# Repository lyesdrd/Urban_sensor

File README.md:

# Urban_sensor
Project of embeded crosswalk recognition

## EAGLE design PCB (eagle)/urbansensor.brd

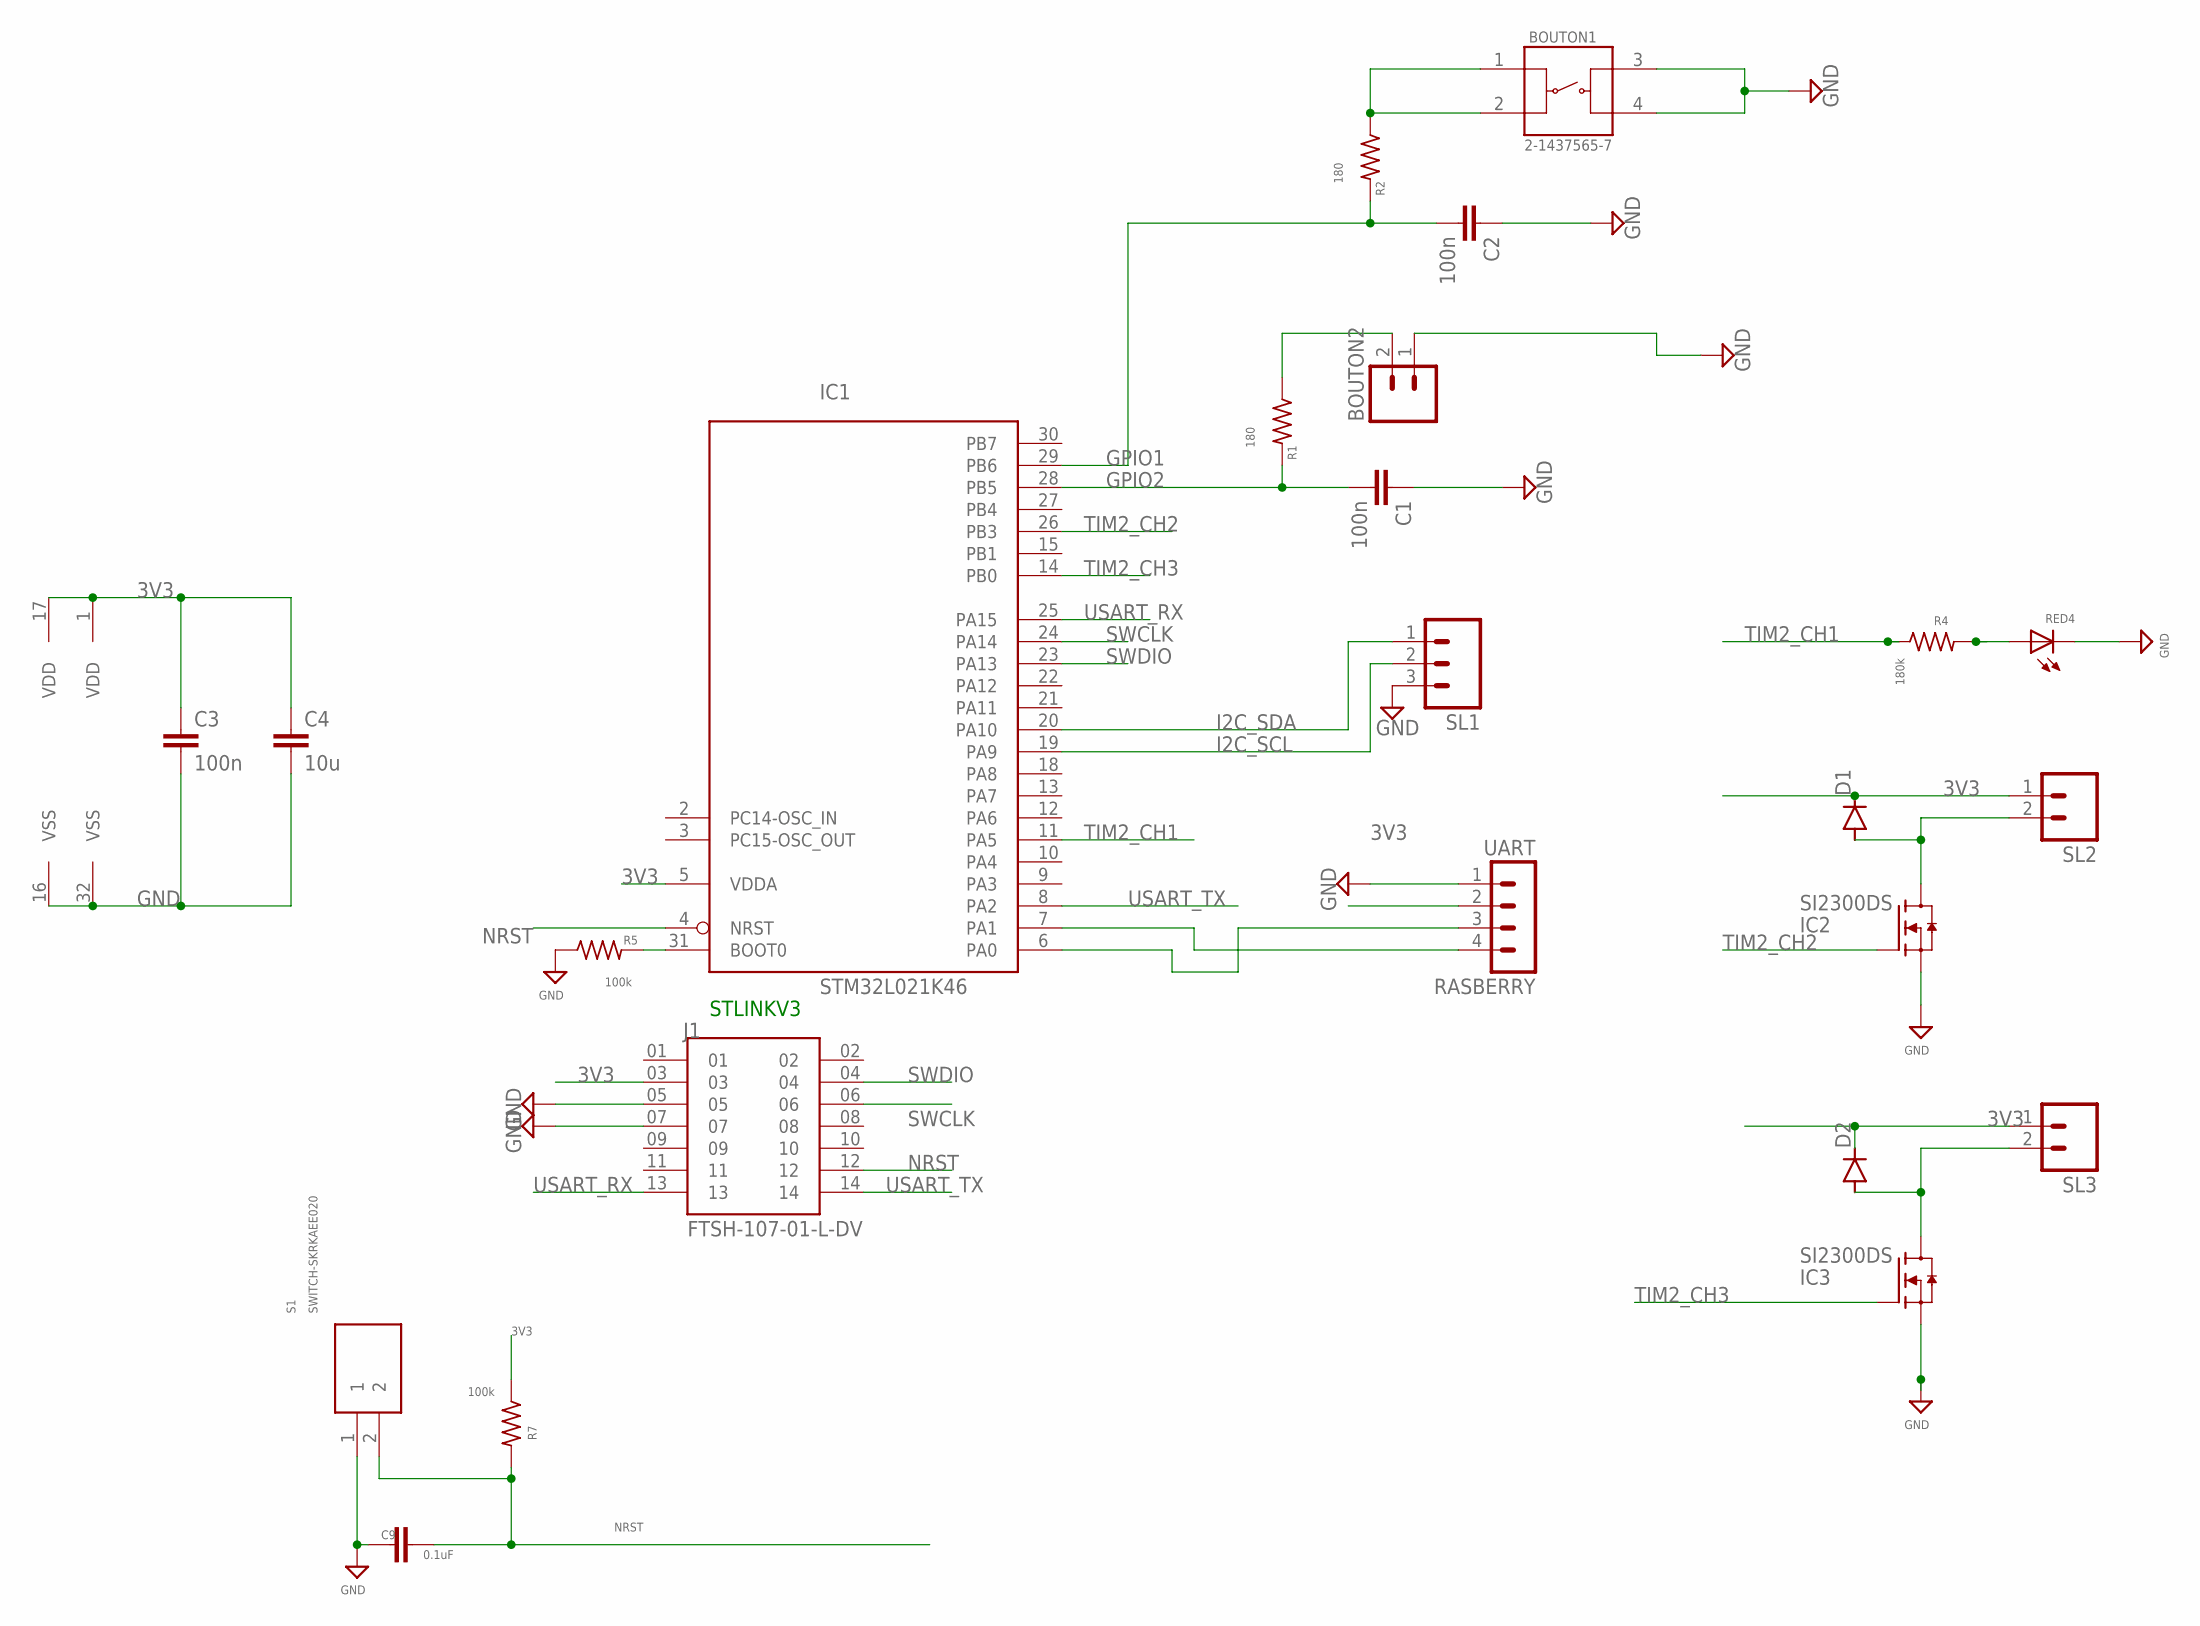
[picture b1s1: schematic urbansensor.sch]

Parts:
BOUTON1: 2-1437565-7; SW_2-1437565-7
BOUTON2: MA02; 02PA
C1, C2, C3: 100n; C0805
C4: 10u; C1210
C9: 0.1uF; 1206
D1, D2: DIODE-SOD523; SOD523
IC1: STM32L021K46; LQFP32
IC2, IC3: SI2300DS; SOT23
J1: FTSH-107-01-L-DV; SAMTEC_FTSH-107-01-L-DV
R1, R2: 180; R0805
R4: 180k; R0805
R5, R7: 100k; R0805
RASBERRY: UART; MA04-1
RED4: LED-0603; 0603-LED
S1: SWITCH-SKRKAEE020; SKRKAEE020
SL1: MA03; 03P
SL2, SL3: MA02; 02PA

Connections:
3V3: C3.1, C4.1, D1.C, D2.C, IC1.1 (VDD), IC1.5 (VDDA), IC1.17 (VDD), J1.03, R7.1, RASBERRY.2, SL2.1, SL3.1
GND: BOUTON1.3, BOUTON1.4, BOUTON2.1, C1.1, C2.1, C3.2, C4.2, C9.1, IC1.16 (VSS), IC1.32 (VSS), IC2.2 (S), IC3.2 (S), J1.05, J1.07, R5.1, RASBERRY.1, RED4.C, S1.1, SL1.3
GPIO1: C2.2, IC1.29 (PB6), R2.2
GPIO2: C1.2, IC1.28 (PB5), R1.2
I2C_SCL: IC1.19 (PA9), SL1.2
I2C_SDA: IC1.20 (PA10), SL1.1
LED_RD4: R4.2, RED4.A
unnamed: IC1.7 (PA1), RASBERRY.4
unnamed: BOUTON2.2, R1.1
unnamed: BOUTON1.1, BOUTON1.2, R2.1
unnamed: D1.A, IC2.3 (D), SL2.2
unnamed: IC1.31 (BOOT0), R5.2
unnamed: D2.A, IC3.3 (D), SL3.2
unnamed: IC1.6 (PA0), RASBERRY.3
NRST: C9.2, IC1.4 (NRST), J1.12, R7.2, S1.2
SWCLK: IC1.24 (PA14), J1.06
SWDIO: IC1.23 (PA13), J1.04
TIM2_CH1: IC1.11 (PA5), R4.1
TIM2_CH2: IC1.26 (PB3), IC2.1 (G)
TIM2_CH3: IC1.14 (PB0), IC3.1 (G)
USART_RX: IC1.25 (PA15), J1.13
USART_TX: IC1.8 (PA2), J1.14

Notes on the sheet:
STLINKV3

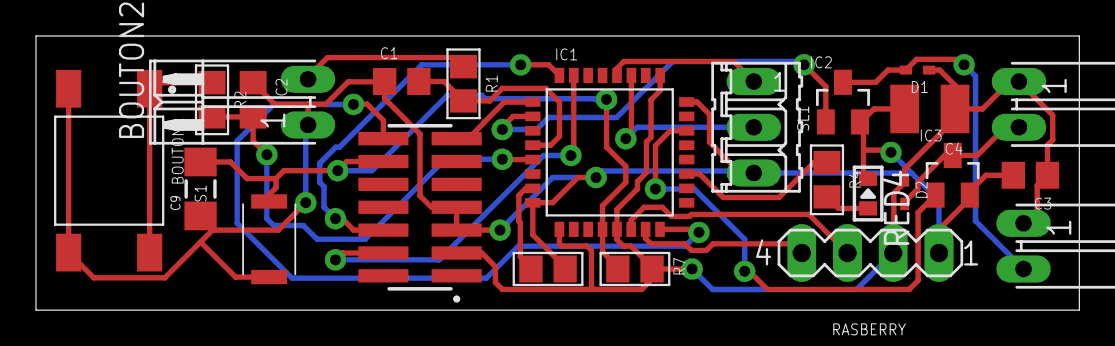
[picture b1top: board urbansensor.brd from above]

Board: 2 copper layers, 58.0 x 15.2 mm, 24 parts (0 on the bottom side), 22 nets.

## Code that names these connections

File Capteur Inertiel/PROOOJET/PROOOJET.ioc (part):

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Mcu.Name=STM32L021K4Tx
Mcu.Package=LQFP32
Mcu.UserName=STM32L021K4Tx
PA10.Mode=I2C
PA10.Signal=I2C1_SDA
PA13.Mode=Serial_Wire
PA13.Signal=SYS_SWDIO
PA14.Mode=Serial_Wire
PA14.Signal=SYS_SWCLK
PA5.Signal=GPIO_Output
PA9.Mode=I2C
PA9.Signal=I2C1_SCL
PB0.Signal=S_TIM2_CH3
PB3.Signal=S_TIM2_CH2
PB5.Signal=GPXTI5
PB6.Signal=GPIO_Output
RCC.HSE_VALUE=8000000
RCC.SYSCLKFreq_VALUE=2097000
board=custom

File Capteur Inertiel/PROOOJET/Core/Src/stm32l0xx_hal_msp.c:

/* USER CODE BEGIN Header */
/**
  ******************************************************************************
  * @file         stm32l0xx_hal_msp.c
  * @brief        This file provides code for the MSP Initialization
  *               and de-Initialization codes.
  ******************************************************************************
  * @attention
  *
  * <h2><center>&copy; Copyright (c) 2022 STMicroelectronics.
  * All rights reserved.</center></h2>
  *
  * This software component is licensed by ST under BSD 3-Clause license,
  * the "License"; You may not use this file except in compliance with the
  * License. You may obtain a copy of the License at:
  *                        opensource.org/licenses/BSD-3-Clause
  *
  ******************************************************************************
  */
/* USER CODE END Header */

/* Includes ------------------------------------------------------------------*/
#include "main.h"
/* USER CODE BEGIN Includes */

/* USER CODE END Includes */

/* Private typedef -----------------------------------------------------------*/
/* USER CODE BEGIN TD */

/* USER CODE END TD */

/* Private define ------------------------------------------------------------*/
/* USER CODE BEGIN Define */

/* USER CODE END Define */

/* Private macro -------------------------------------------------------------*/
/* USER CODE BEGIN Macro */

/* USER CODE END Macro */

/* Private variables ---------------------------------------------------------*/
/* USER CODE BEGIN PV */

/* USER CODE END PV */

/* Private function prototypes -----------------------------------------------*/
/* USER CODE BEGIN PFP */

/* USER CODE END PFP */

/* External functions --------------------------------------------------------*/
/* USER CODE BEGIN ExternalFunctions */

/* USER CODE END ExternalFunctions */

/* USER CODE BEGIN 0 */

/* USER CODE END 0 */

void HAL_TIM_MspPostInit(TIM_HandleTypeDef *htim);
                    /**
  * Initializes the Global MSP.
  */
void HAL_MspInit(void)
{
  /* USER CODE BEGIN MspInit 0 */

  /* USER CODE END MspInit 0 */

  __HAL_RCC_SYSCFG_CLK_ENABLE();
  __HAL_RCC_PWR_CLK_ENABLE();

  /* System interrupt init*/

  /* USER CODE BEGIN MspInit 1 */

  /* USER CODE END MspInit 1 */
}

/**
* @brief I2C MSP Initialization
* This function configures the hardware resources used in this example
* @param hi2c: I2C handle pointer
* @retval None
*/
void HAL_I2C_MspInit(I2C_HandleTypeDef* hi2c)
{
  GPIO_InitTypeDef GPIO_InitStruct = {0};
  if(hi2c->Instance==I2C1)
  {
  /* USER CODE BEGIN I2C1_MspInit 0 */

  /* USER CODE END I2C1_MspInit 0 */

    __HAL_RCC_GPIOA_CLK_ENABLE();
    /**I2C1 GPIO Configuration
    PA9     ------> I2C1_SCL
    PA10     ------> I2C1_SDA
    */
    GPIO_InitStruct.Pin = GPIO_PIN_9|GPIO_PIN_10;
    GPIO_InitStruct.Mode = GPIO_MODE_AF_OD;
    GPIO_InitStruct.Pull = GPIO_NOPULL;
    GPIO_InitStruct.Speed = GPIO_SPEED_FREQ_VERY_HIGH;
    GPIO_InitStruct.Alternate = GPIO_AF1_I2C1;
    HAL_GPIO_Init(GPIOA, &GPIO_InitStruct);

    /* Peripheral clock enable */
    __HAL_RCC_I2C1_CLK_ENABLE();
    /* I2C1 interrupt Init */
    HAL_NVIC_SetPriority(I2C1_IRQn, 0, 0);
    HAL_NVIC_EnableIRQ(I2C1_IRQn);
  /* USER CODE BEGIN I2C1_MspInit 1 */

  /* USER CODE END I2C1_MspInit 1 */
  }

}

/**
* @brief I2C MSP De-Initialization
* This function freeze the hardware resources used in this example
* @param hi2c: I2C handle pointer
* @retval None
*/
void HAL_I2C_MspDeInit(I2C_HandleTypeDef* hi2c)
{
  if(hi2c->Instance==I2C1)
  {
  /* USER CODE BEGIN I2C1_MspDeInit 0 */

  /* USER CODE END I2C1_MspDeInit 0 */
    /* Peripheral clock disable */
    __HAL_RCC_I2C1_CLK_DISABLE();

    /**I2C1 GPIO Configuration
    PA9     ------> I2C1_SCL
    PA10     ------> I2C1_SDA
    */
    HAL_GPIO_DeInit(GPIOA, GPIO_PIN_9);

    HAL_GPIO_DeInit(GPIOA, GPIO_PIN_10);

    /* I2C1 interrupt DeInit */
    HAL_NVIC_DisableIRQ(I2C1_IRQn);
  /* USER CODE BEGIN I2C1_MspDeInit 1 */

  /* USER CODE END I2C1_MspDeInit 1 */
  }

}

/**
* @brief TIM_PWM MSP Initialization
* This function configures the hardware resources used in this example
* @param htim_pwm: TIM_PWM handle pointer
* @retval None
*/
void HAL_TIM_PWM_MspInit(TIM_HandleTypeDef* htim_pwm)
{
  if(htim_pwm->Instance==TIM2)
  {
  /* USER CODE BEGIN TIM2_MspInit 0 */

  /* USER CODE END TIM2_MspInit 0 */
    /* Peripheral clock enable */
    __HAL_RCC_TIM2_CLK_ENABLE();
    /* TIM2 interrupt Init */
    HAL_NVIC_SetPriority(TIM2_IRQn, 0, 0);
    HAL_NVIC_EnableIRQ(TIM2_IRQn);
  /* USER CODE BEGIN TIM2_MspInit 1 */

  /* USER CODE END TIM2_MspInit 1 */
  }

}

/**
* @brief TIM_Base MSP Initialization
* This function configures the hardware resources used in this example
* @param htim_base: TIM_Base handle pointer
* @retval None
*/
void HAL_TIM_Base_MspInit(TIM_HandleTypeDef* htim_base)
{
  if(htim_base->Instance==TIM21)
  {
  /* USER CODE BEGIN TIM21_MspInit 0 */

  /* USER CODE END TIM21_MspInit 0 */
    /* Peripheral clock enable */
    __HAL_RCC_TIM21_CLK_ENABLE();
    /* TIM21 interrupt Init */
    HAL_NVIC_SetPriority(TIM21_IRQn, 0, 0);
    HAL_NVIC_EnableIRQ(TIM21_IRQn);
  /* USER CODE BEGIN TIM21_MspInit 1 */

  /* USER CODE END TIM21_MspInit 1 */
  }

}

void HAL_TIM_MspPostInit(TIM_HandleTypeDef* htim)
{
  GPIO_InitTypeDef GPIO_InitStruct = {0};
  if(htim->Instance==TIM2)
  {
  /* USER CODE BEGIN TIM2_MspPostInit 0 */

  /* USER CODE END TIM2_MspPostInit 0 */

    __HAL_RCC_GPIOB_CLK_ENABLE();
    /**TIM2 GPIO Configuration
    PB0     ------> TIM2_CH3
    PB3     ------> TIM2_CH2
    */
    GPIO_InitStruct.Pin = GPIO_PIN_0;
    GPIO_InitStruct.Mode = GPIO_MODE_AF_PP;
    GPIO_InitStruct.Pull = GPIO_NOPULL;
    GPIO_InitStruct.Speed = GPIO_SPEED_FREQ_LOW;
    GPIO_InitStruct.Alternate = GPIO_AF5_TIM2;
    HAL_GPIO_Init(GPIOB, &GPIO_InitStruct);

    GPIO_InitStruct.Pin = GPIO_PIN_3;
    GPIO_InitStruct.Mode = GPIO_MODE_AF_PP;
    GPIO_InitStruct.Pull = GPIO_NOPULL;
    GPIO_InitStruct.Speed = GPIO_SPEED_FREQ_LOW;
    GPIO_InitStruct.Alternate = GPIO_AF2_TIM2;
    HAL_GPIO_Init(GPIOB, &GPIO_InitStruct);

  /* USER CODE BEGIN TIM2_MspPostInit 1 */

  /* USER CODE END TIM2_MspPostInit 1 */
  }

}
/**
* @brief TIM_PWM MSP De-Initialization
* This function freeze the hardware resources used in this example
* @param htim_pwm: TIM_PWM handle pointer
* @retval None
*/
void HAL_TIM_PWM_MspDeInit(TIM_HandleTypeDef* htim_pwm)
{
  if(htim_pwm->Instance==TIM2)
  {
  /* USER CODE BEGIN TIM2_MspDeInit 0 */

  /* USER CODE END TIM2_MspDeInit 0 */
    /* Peripheral clock disable */
    __HAL_RCC_TIM2_CLK_DISABLE();

    /* TIM2 interrupt DeInit */
    HAL_NVIC_DisableIRQ(TIM2_IRQn);
  /* USER CODE BEGIN TIM2_MspDeInit 1 */

  /* USER CODE END TIM2_MspDeInit 1 */
  }

}

/**
* @brief TIM_Base MSP De-Initialization
* This function freeze the hardware resources used in this example
* @param htim_base: TIM_Base handle pointer
* @retval None
*/
void HAL_TIM_Base_MspDeInit(TIM_HandleTypeDef* htim_base)
{
  if(htim_base->Instance==TIM21)
  {
  /* USER CODE BEGIN TIM21_MspDeInit 0 */

  /* USER CODE END TIM21_MspDeInit 0 */
    /* Peripheral clock disable */
    __HAL_RCC_TIM21_CLK_DISABLE();

    /* TIM21 interrupt DeInit */
    HAL_NVIC_DisableIRQ(TIM21_IRQn);
  /* USER CODE BEGIN TIM21_MspDeInit 1 */

  /* USER CODE END TIM21_MspDeInit 1 */
  }

}

/* USER CODE BEGIN 1 */

/* USER CODE END 1 */

/************************ (C) COPYRIGHT STMicroelectronics *****END OF FILE****/

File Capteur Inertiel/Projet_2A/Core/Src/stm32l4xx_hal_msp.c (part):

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
    __HAL_RCC_GPIOA_CLK_ENABLE();
    /**I2C1 GPIO Configuration
    PA9     ------> I2C1_SCL
    PA10     ------> I2C1_SDA
    */
    GPIO_InitStruct.Pin = GPIO_PIN_9|GPIO_PIN_10;
    GPIO_InitStruct.Mode = GPIO_MODE_AF_OD;
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    __HAL_RCC_I2C1_CLK_DISABLE();

    /**I2C1 GPIO Configuration
    PA9     ------> I2C1_SCL
    PA10     ------> I2C1_SDA
    */
    HAL_GPIO_DeInit(GPIOA, GPIO_PIN_9);

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
    __HAL_RCC_GPIOA_CLK_ENABLE();
    /**TIM2 GPIO Configuration
    PA5     ------> TIM2_CH1
    */
    GPIO_InitStruct.Pin = GPIO_PIN_5;
    GPIO_InitStruct.Mode = GPIO_MODE_AF_PP;
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
    __HAL_RCC_GPIOA_CLK_ENABLE();
    /**USART2 GPIO Configuration
    PA2     ------> USART2_TX
    PA15 (JTDI)     ------> USART2_RX
    */
    GPIO_InitStruct.Pin = VCP_TX_Pin;
    GPIO_InitStruct.Mode = GPIO_MODE_AF_PP;
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    __HAL_RCC_USART2_CLK_DISABLE();

    /**USART2 GPIO Configuration
    PA2     ------> USART2_TX
    PA15 (JTDI)     ------> USART2_RX
    */
    HAL_GPIO_DeInit(GPIOA, VCP_TX_Pin|VCP_RX_Pin);

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
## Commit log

2022-04-27 camera part without the video of the real time processing
2022-05-01 Ajout de la partie IA
2022-05-02 ajout des fichiers eagle
2022-05-06 ajout des fichiers du capteur inertiel

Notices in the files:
Capteur Inertiel/Projet_2A/Core/Src/stm32l4xx_hal_msp.c:
© Copyright (c) 2021 STMicroelectronics.
All rights reserved.
